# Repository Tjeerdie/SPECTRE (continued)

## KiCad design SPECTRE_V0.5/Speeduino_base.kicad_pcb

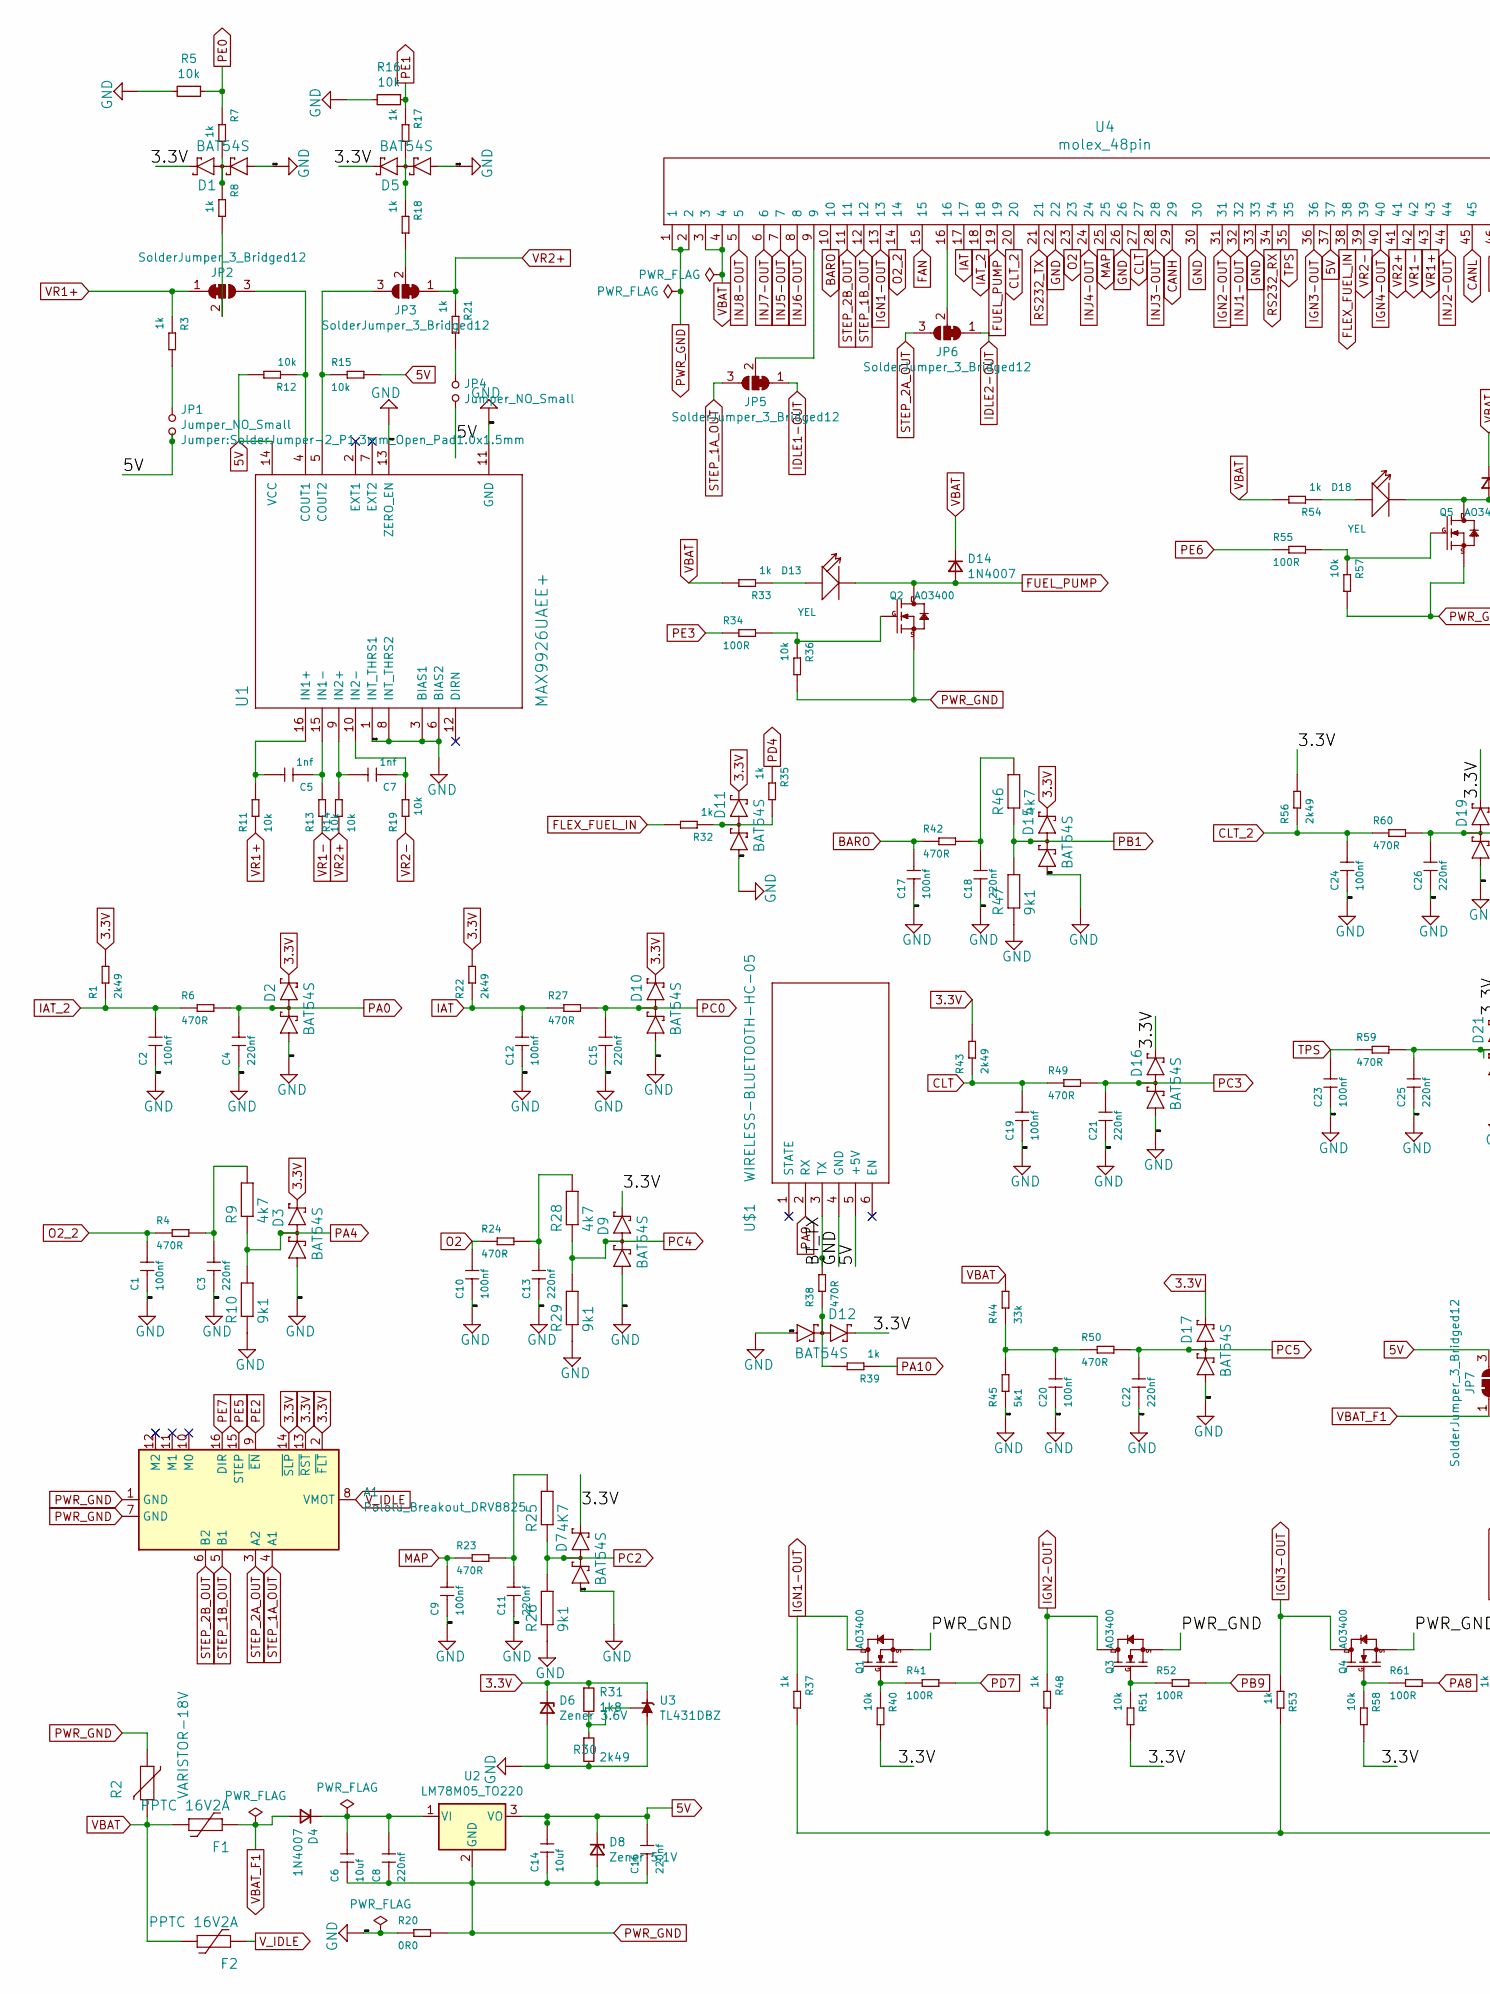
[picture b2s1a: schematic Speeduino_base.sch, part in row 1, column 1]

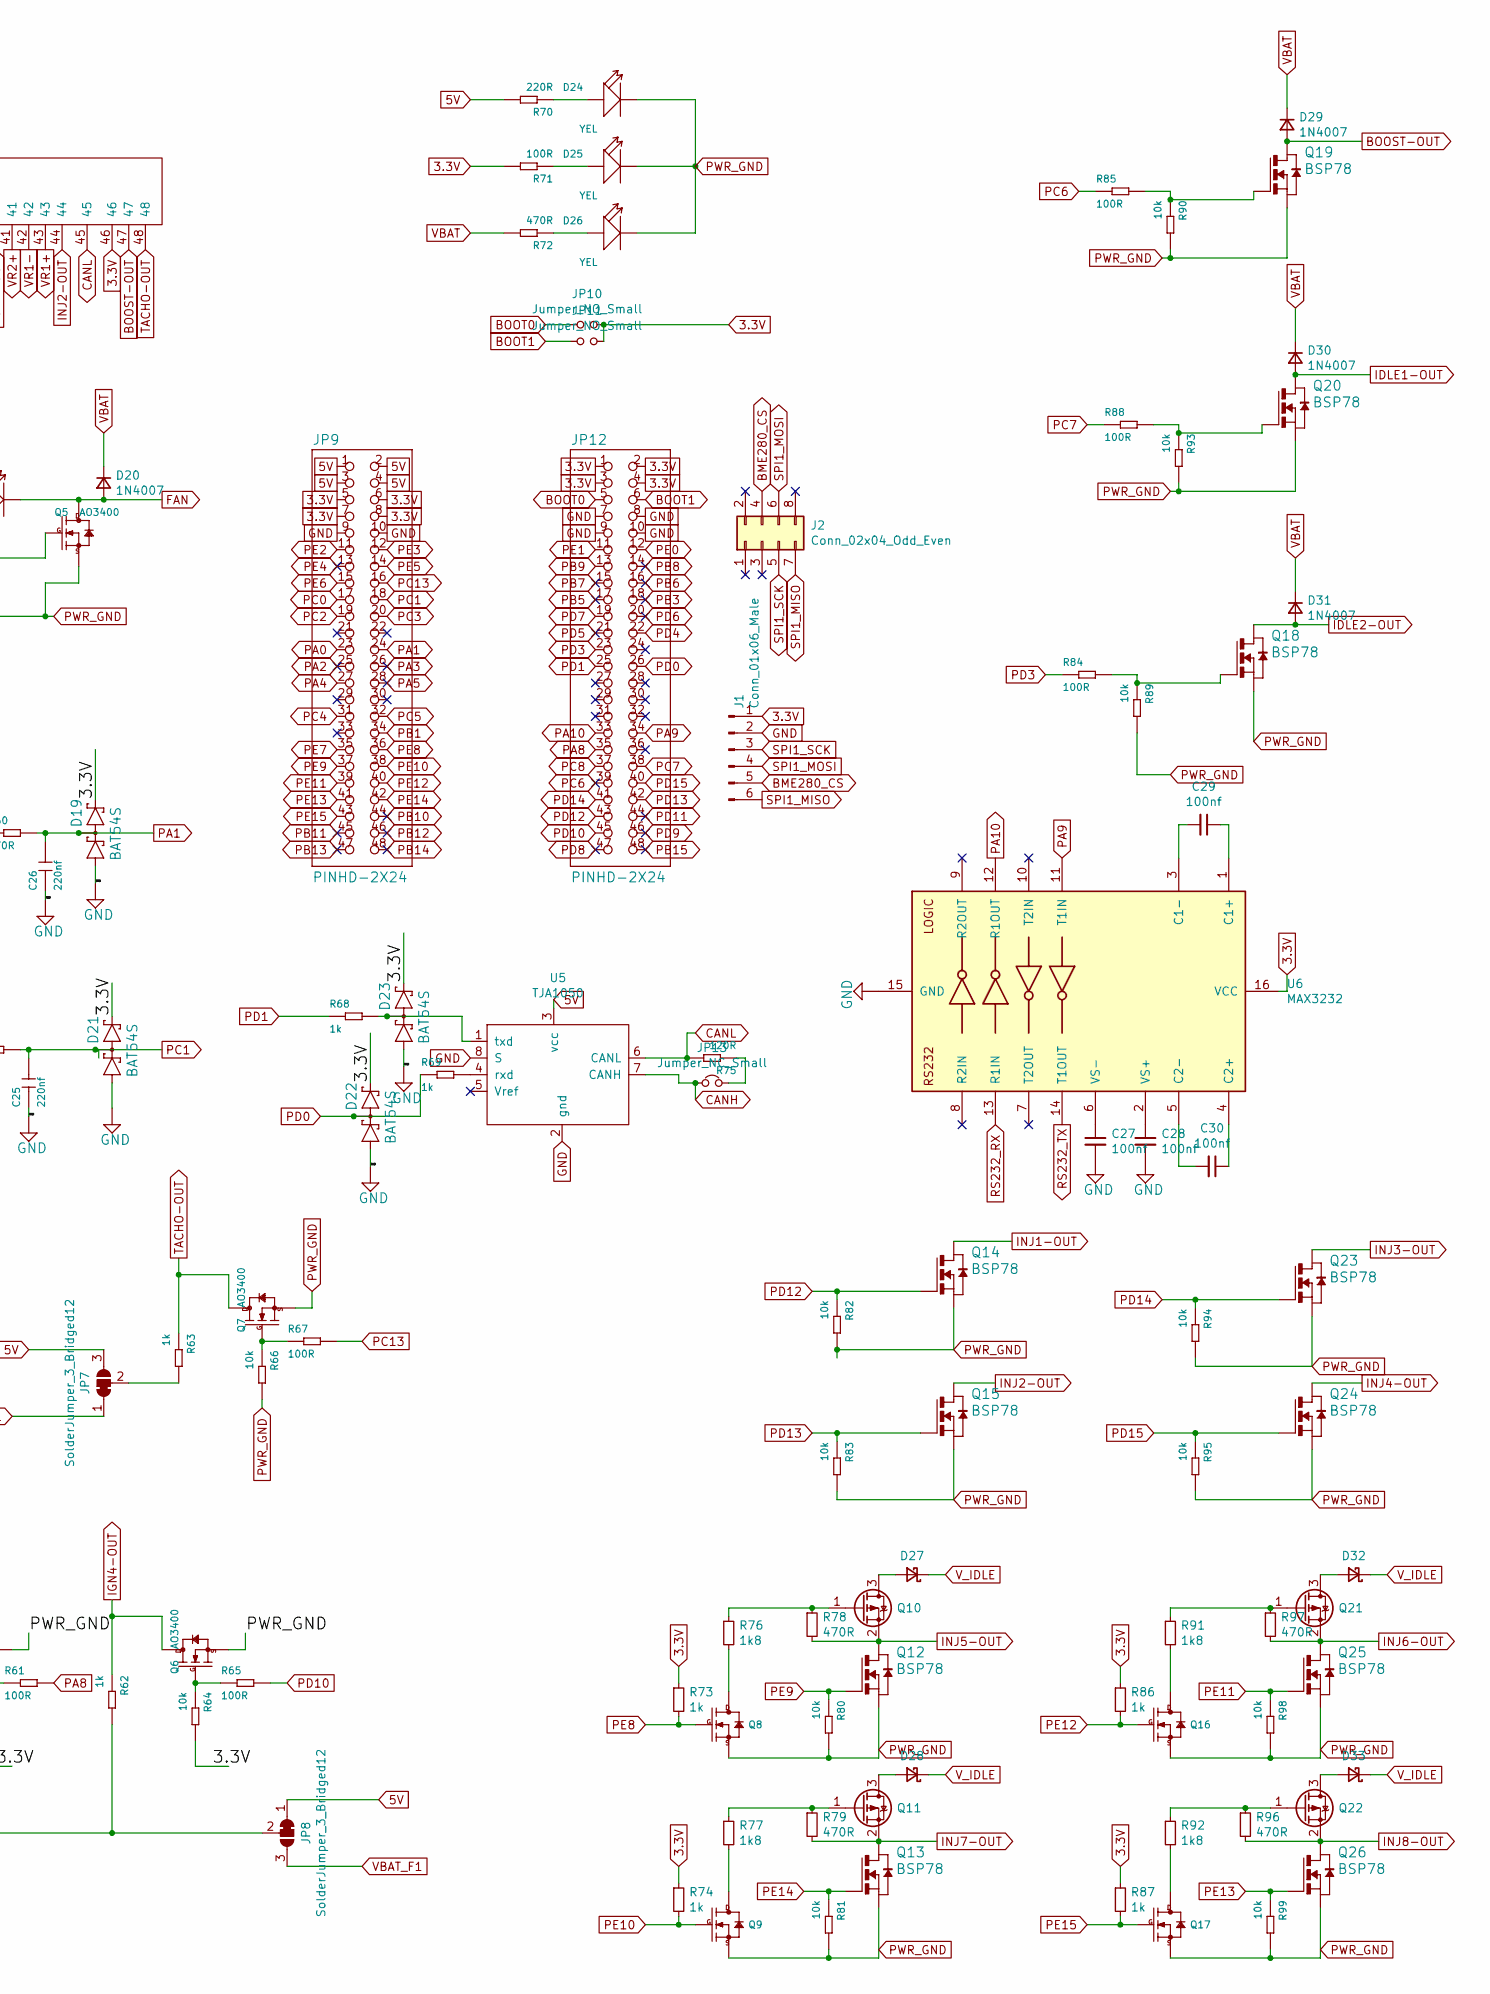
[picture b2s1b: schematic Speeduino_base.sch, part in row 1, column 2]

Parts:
A1: Pololu_Breakout_DRV8825; Pololu_Breakout-16_15.2x20.3mm
C1, C2, C9, C10, C12, C17, C19, C20, C23, C24, C27, C28, C29, C30: 100nf; C0603
C3, C4, C8, C11, C13, C15, C16, C18, C21, C22, C25, C26: 220nf; C0603
C5, C7: 1nf; C0603
C6, C14: 10uf; C1206
D1, D2, D3, D5, D7, D9, D10, D11, D12, D15, D16, D17, D19, D21, D22, D23: BAT54S; SOT23
D4, D14, D20, D27, D28, D29, D30, D31, D32, D33: 1N4007; D_SMA
D6: Zener 3.6V; D_MiniMELF_Handsoldering
D8: Zener 5.1V; D_MiniMELF_Handsoldering
D13, D18, D24, D25, D26: YEL; LED-0603
F1, F2: PPTC 16V2A; R_1812_4532Metric_Pad1.30x3.40mm_HandSolder
J1: Conn_01x06_Male; PinHeader_1x06_P2.54mm_Vertical
J2: Conn_02x04_Odd_Even; PinHeader_2x04_P2.54mm_Vertical
JP1, JP4: Jumper_NO_Small; SolderJumper-2_P1.3mm_Open_Pad1.0x1.5mm
JP2, JP3, JP5, JP6, JP7, JP8: SolderJumper_3_Bridged12; SolderJumper-3_P1.3mm_Bridged12_Pad1.0x1.5mm
JP9, JP12: PINHD-2X24; 2X24
JP10, JP11: Jumper_NO_Small; PinHeader_1x02_P2.54mm_Vertical
JP13: Jumper_NC_Small; SolderJumper-2_P1.3mm_Bridged_Pad1.0x1.5mm
Q1, Q2, Q3, Q4, Q5, Q6, Q7: AO3400; SOT-23
Q8, Q9, Q16, Q17: AO3422; SOT-23_Handsoldering
Q10, Q11, Q21, Q22: AO3401A; SOT-23_Handsoldering
Q12, Q13, Q14, Q15, Q18, Q19, Q20, Q23, Q24, Q25, Q26: BSP78; SOT223
R1, R22, R30, R43, R56: 2k49; R0603
R2: VARISTOR-18V; RV_Disc_D12mm_W3.9mm_P7.5mm
R3, R7, R8, R17, R18, R21, R32, R33, R35, R37, R39, R48, R53, R54, R62, R63, R68, R69, R73, R74, R86, R87: 1k; R0603
R4, R6, R23, R24, R27, R38, R42, R49, R50, R59, R60, R72, R78, R79, R96, R97: 470R; R0603
R5, R11, R12, R13, R14, R15, R16, R19, R36, R40, R51, R57, R58, R64, R66, R80, R81, R82, R83, R89, R90, R93, R94, R95, R98, R99: 10k; R0603
R9, R28, R46: 4k7; R0603
R10, R26, R29, R47: 9k1; R0603
R20: 0R0; R0603
R25: 4K7; R0603
R31, R76, R77, R91, R92: 1k8; R0603
R34, R41, R52, R55, R61, R65, R67, R71, R84, R85, R88: 100R; R0603
R44: 33k; R0603
R45: 5k1; R0603
R70: 220R; R0603
R75: 120R; R0603
U1: MAX9926UAEE+; 21-0055H_16
U2: LM78M05_TO220; TO-220-3_Vertical
U3: TL431DBZ; SOT-23
U4: molex_48pin; Molex_48
U5: TJA1050; SO-8_5.3x6.2mm_P1.27mm
U6: MAX3232; SOIC-16_4.55x10.3mm_P1.27mm
U$1: WIRELESS-BLUETOOTH-HC-05

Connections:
3.3V: A1.2 (~FLT), A1.13 (~RST), A1.14 (~SLP), D1.2 (C2), D2.2 (C2), D3.2 (C2), D5.2 (C2), D6.1 (K), D7.2 (C2), D9.2 (C2), D10.2 (C2), D11.2 (C2), D12.2 (C2), D15.2 (C2), D16.2 (C2), D17.2 (C2), D19.2 (C2), D21.2 (C2), D22.2 (C2), D23.2 (C2), J1.1, JP9.5, JP9.6, JP9.7, JP9.8, JP10.2, JP11.2, JP12.1, JP12.2, JP12.3, JP12.4, R1.2, R22.2, R31.1, R40.2, R43.2, R51.2, R56.2, R58.2, R64.2, R71.2, R73.1, R74.1, R86.1, R87.1, U3.1 (K), U4.46, U6.16 (VCC)
5V: C14.2, C16.2, D8.1 (K), JP1.2, JP4.2, JP7.3 (B), JP8.1 (A), JP9.1, JP9.2, JP9.3, JP9.4, R12.2, R15.2, R70.2, U1.14 (VCC), U2.3 (VO), U4.37, U5.3 (vcc), U$1.5 (+5V)
/BT_TX: R38.2, U$1.3 (TX)
AIN_1: C2.2, R1.1, R6.1, U4.18
AIN_2: C1.2, R4.1, U4.14
AIN_3: C24.2, R56.1, R60.1, U4.20
BARO: C17.2, R42.1, U4.10
BME280_CS: J1.5, J2.4
BOOST-OUT: D29.2 (A), Q19.2 (D), Q19.4 (D), U4.47
BOOT0: JP10.1, JP12.5
BOOT1: JP11.1, JP12.6
CANH: JP13.1, U4.29, U5.7 (CANH)
CANL: R75.2, U4.45, U5.6 (CANL)
CLT: C19.2, R43.1, R49.1, U4.27
FAN: D18.-, D20.2 (A), Q5.3 (D), U4.15
FLEX_FUEL_IN: R32.2, U4.38
FUEL_PUMP: D13.-, D14.2 (A), Q2.3 (D), U4.19
GND: C1.1, C2.1, C3.1, C4.1, C9.1, C10.1, C11.1, C12.1, C13.1, C15.1, C17.1, C18.1, C19.1, C20.1, C21.1, C22.1, C23.1, C24.1, C25.1, C26.1, C27.2, C28.2, D1.1 (A1), D2.1 (A1), D3.1 (A1), D5.1 (A1), D6.2 (A), D7.1 (A1), D9.1 (A1), D10.1 (A1), D11.1 (A1), D12.1 (A1), D15.1 (A1), D16.1 (A1), D17.1 (A1), D19.1 (A1), D21.1 (A1), D22.1 (A1), D23.1 (A1), J1.2, JP9.9, JP9.10, JP12.7, JP12.8, JP12.9, JP12.10, R5.2, R10.1, R16.2, R20.1, R26.1, R29.1, R30.2, R45.1, R47.1, U1.1 (INT_THRS1), U1.3 (BIAS1), U1.6 (BIAS2), U1.8 (INT_THRS2), U1.11 (GND), U1.13 (ZERO_EN), U3.3 (A), U4.22, U4.26, U4.30, U4.33, U5.2 (gnd), U5.8 (S), U6.15 (GND), U$1.4 (GND)
IAT: C12.2, R22.1, R27.1, U4.17
IDLE1-OUT: D30.2 (A), JP5.1 (A), Q20.2 (D), Q20.4 (D)
IDLE2-OUT: D31.2 (A), JP6.1 (A), Q18.2 (D), Q18.4 (D)
IGN1-OUT: Q1.3 (D), R37.1, U4.13
IGN2-OUT: Q3.3 (D), R48.1, U4.31
IGN3-OUT: Q4.3 (D), R53.1, U4.36
IGN4-OUT: Q6.3 (D), R62.1, U4.40
INJ1-OUT: Q14.2 (D), Q14.4 (D), U4.32
INJ2-OUT: Q15.2 (D), Q15.4 (D), U4.44
INJ3-OUT: Q23.2 (D), Q23.4 (D), U4.28
INJ4-OUT: Q24.2 (D), Q24.4 (D), U4.24
INJ5-OUT: Q10.2 (S), Q12.2 (D), Q12.4 (D), R78.2, U4.7
INJ6-OUT: Q21.2 (S), Q25.2 (D), Q25.4 (D), R97.2, U4.8
INJ7-OUT: Q11.2 (S), Q13.2 (D), Q13.4 (D), R79.2, U4.6
INJ8-OUT: Q22.2 (S), Q26.2 (D), Q26.4 (D), R96.2, U4.5
MAP: C9.2, R23.1, U4.25
unnamed: C3.2, R4.2, R9.2
unnamed: C5.1, R13.2, U1.15 (IN1-)
unnamed: C5.2, R11.2, U1.16 (IN1+)
unnamed: C6.2, C8.2, D4.1 (K), U2.1 (VI)
unnamed: C7.1, R19.2, U1.10 (IN2-)
unnamed: C7.2, R14.2, U1.9 (IN2+)
unnamed: C11.2, R23.2, R25.2
unnamed: C13.2, R24.2, R28.2
unnamed: C18.2, R42.2, R46.2
unnamed: C20.2, R44.1, R45.2, R50.1
unnamed: C27.1, U6.6 (VS-)
unnamed: C28.1, U6.2 (VS+)
unnamed: C29.1, U6.1 (C1+)
unnamed: C29.2, U6.3 (C1-)
unnamed: C30.1, U6.4 (C2+)
unnamed: C30.2, U6.5 (C2-)
unnamed: D1.3 (C1A2), R7.2, R8.1
unnamed: D5.3 (C1A2), R17.2, R18.1
unnamed: D11.3 (C1A2), R32.1, R35.2
unnamed: D12.3 (C1A2), R38.1, R39.2
unnamed: D13.+, R33.1
unnamed: D18.+, R54.1
unnamed: D23.3 (C1A2), R68.2, U5.1 (txd)
unnamed: D24.+, R70.1
unnamed: D25.+, R71.1
unnamed: D26.+, R72.1
unnamed: D27.2 (A), Q10.3 (D)
unnamed: D28.2 (A), Q11.3 (D)
unnamed: D32.2 (A), Q21.3 (D)
unnamed: D33.2 (A), Q22.3 (D)
unnamed: JP1.1, R3.2
unnamed: JP2.2 (C), R8.2
unnamed: JP2.3 (B), R12.1, U1.4 (COUT1)
unnamed: JP3.2 (C), R18.2
unnamed: JP3.3 (B), R15.1, U1.5 (COUT2)
unnamed: JP4.1, R21.2
unnamed: JP5.2 (C), U4.9
unnamed: JP6.2 (C), U4.16
unnamed: JP7.2 (C), R63.2
unnamed: JP8.2 (C), R37.2, R48.2, R53.2, R62.2
unnamed: JP13.2, R75.1
unnamed: Q1.1 (G), R40.1, R41.1
unnamed: Q2.1 (G), R34.2, R36.1
unnamed: Q3.1 (G), R51.1, R52.1
unnamed: Q4.1 (G), R58.1, R61.1
unnamed: Q5.1 (G), R55.2, R57.1
unnamed: Q6.1 (G), R64.1, R65.1
unnamed: Q7.1 (G), R66.1, R67.1
unnamed: Q8.3 (D), R76.2
unnamed: Q9.3 (D), R77.2
unnamed: Q10.1 (G), R76.1, R78.1
unnamed: Q11.1 (G), R77.1, R79.1
unnamed: Q16.3 (D), R91.2
unnamed: Q17.3 (D), R92.2
unnamed: Q18.1 (G), R84.2, R89.1
unnamed: Q19.1 (G), R85.2, R90.1
unnamed: Q20.1 (G), R88.2, R93.1
unnamed: Q21.1 (G), R91.1, R97.1
unnamed: Q22.1 (G), R92.1, R96.1
unnamed: R30.1, R31.2, U3.2 (REF)
unnamed: R69.2, U5.4 (rxd)
O2: C10.2, R24.1, U4.23
PA0: C4.2, D2.3 (C1A2), JP9.23, R6.2
PA1: C26.2, D19.3 (C1A2), JP9.24, R60.2
PA2: JP9.25
PA3: JP9.26
PA4: D3.3 (C1A2), JP9.27, R9.1, R10.2
PA5: JP9.28
PA8: JP12.35, R61.2
PA9: JP12.34, U6.11 (T1IN), U$1.2 (RX)
PA10: JP12.33, R39.1, U6.12 (R1OUT)
PB1: D15.3 (C1A2), JP9.34, R46.1, R47.2
PB3: JP12.18
PB5: JP12.17
PB6: JP12.16
PB7: JP12.15
PB8: JP12.14
PB9: JP12.13, R52.2
PB10: JP9.44
PB11: JP9.45
PB12: JP9.46
PB13: JP9.47
PB14: JP9.48
PB15: JP12.48
PC0: C15.2, D10.3 (C1A2), JP9.17, R27.2
PC1: C25.2, D21.3 (C1A2), JP9.18, R59.2
PC2: D7.3 (C1A2), JP9.19, R25.1, R26.2
PC3: C21.2, D16.3 (C1A2), JP9.20, R49.2
PC4: D9.3 (C1A2), JP9.31, R28.1, R29.2
PC5: C22.2, D17.3 (C1A2), JP9.32, R50.2
PC6: JP12.39, R85.1
PC7: JP12.38, R88.1
PC8: JP12.37
PC13: JP9.16, R67.2
PD0: D22.3 (C1A2), JP12.26, R69.1
PD1: JP12.25, R68.1
PD3: JP12.23, R84.1
PD4: JP12.22, R35.1
PD5: JP12.21
PD6: JP12.20
PD7: JP12.19, R41.2
PD8: JP12.47
PD9: JP12.46
PD10: JP12.45, R65.2
PD11: JP12.44
PD12: JP12.43, Q14.1 (G), R82.1
PD13: JP12.42, Q15.1 (G), R83.1
PD14: JP12.41, Q23.1 (G), R94.1
PD15: JP12.40, Q24.1 (G), R95.1
PE0: JP12.12, R5.1, R7.1
PE1: JP12.11, R16.1, R17.1
PE2: A1.9 (~EN), JP9.11
PE3: JP9.12, R34.1
PE4: JP9.13
PE5: A1.15 (STEP), JP9.14
PE6: JP9.15, R55.1
PE7: A1.16 (DIR), JP9.35
PE8: JP9.36, Q8.1 (G), R73.2
PE9: JP9.37, Q12.1 (G), R80.1
PE10: JP9.38, Q9.1 (G), R74.2
PE11: JP9.39, Q25.1 (G), R98.1
PE12: JP9.40, Q16.1 (G), R86.2
PE13: JP9.41, Q26.1 (G), R99.1
PE14: JP9.42, Q13.1 (G), R81.1
PE15: JP9.43, Q17.1 (G), R87.2
PWR_GND: A1.1 (GND), A1.7 (GND), C6.1, C8.1, C14.1, C16.1, D8.2 (A), D24.-, D25.-, D26.-, Q1.2 (S), Q2.2 (S), Q3.2 (S), Q4.2 (S), Q5.2 (S), Q6.2 (S), Q7.2 (S), Q8.2 (S), Q9.2 (S), Q12.3 (S), Q13.3 (S), Q14.3 (S), Q15.3 (S), Q16.2 (S), Q17.2 (S), Q18.3 (S), Q19.3 (S), Q20.3 (S), Q23.3 (S), Q24.3 (S), Q25.3 (S), Q26.3 (S), R2.1, R20.2, R36.2, R57.2, R66.2, R80.2, R81.2, R82.2, R83.2, R89.2, R90.2, R93.2, R94.2, R95.2, R98.2, R99.2, U2.2 (GND), U4.1, U4.2
RS232_RX: U4.34, U6.13 (R1IN)
RS232_TX: U4.21, U6.14 (T1OUT)
SPI1_MISO: J1.6, J2.7
SPI1_MOSI: J1.4, J2.6
SPI1_SCK: J1.3, J2.5
STEP_1A_OUT: A1.4 (A1), JP5.3 (B)
STEP_1B_OUT: A1.5 (B1), U4.12
STEP_2A_OUT: A1.3 (A2), JP6.3 (B)
STEP_2B_OUT: A1.6 (B2), U4.11
TACHO-OUT: Q7.3 (D), R63.1, U4.48
TPS: C23.2, R59.1, U4.35
VBAT: D14.1 (K), D20.1 (K), D29.1 (K), D30.1 (K), D31.1 (K), F1.1, F2.1, R2.2, R33.2, R44.2, R54.2, R72.2, U4.3, U4.4
VBAT_F1: D4.2 (A), F1.2, JP7.1 (A), JP8.3 (B)
VR1+: JP2.1 (A), R3.1, R11.1, U4.43
VR1-: R13.1, U4.42
VR2+: JP3.1 (A), R14.1, R21.1, U4.41
VR2-: R19.1, U4.39
V_IDLE: A1.8 (VMOT), D27.1 (K), D28.1 (K), D32.1 (K), D33.1 (K), F2.2

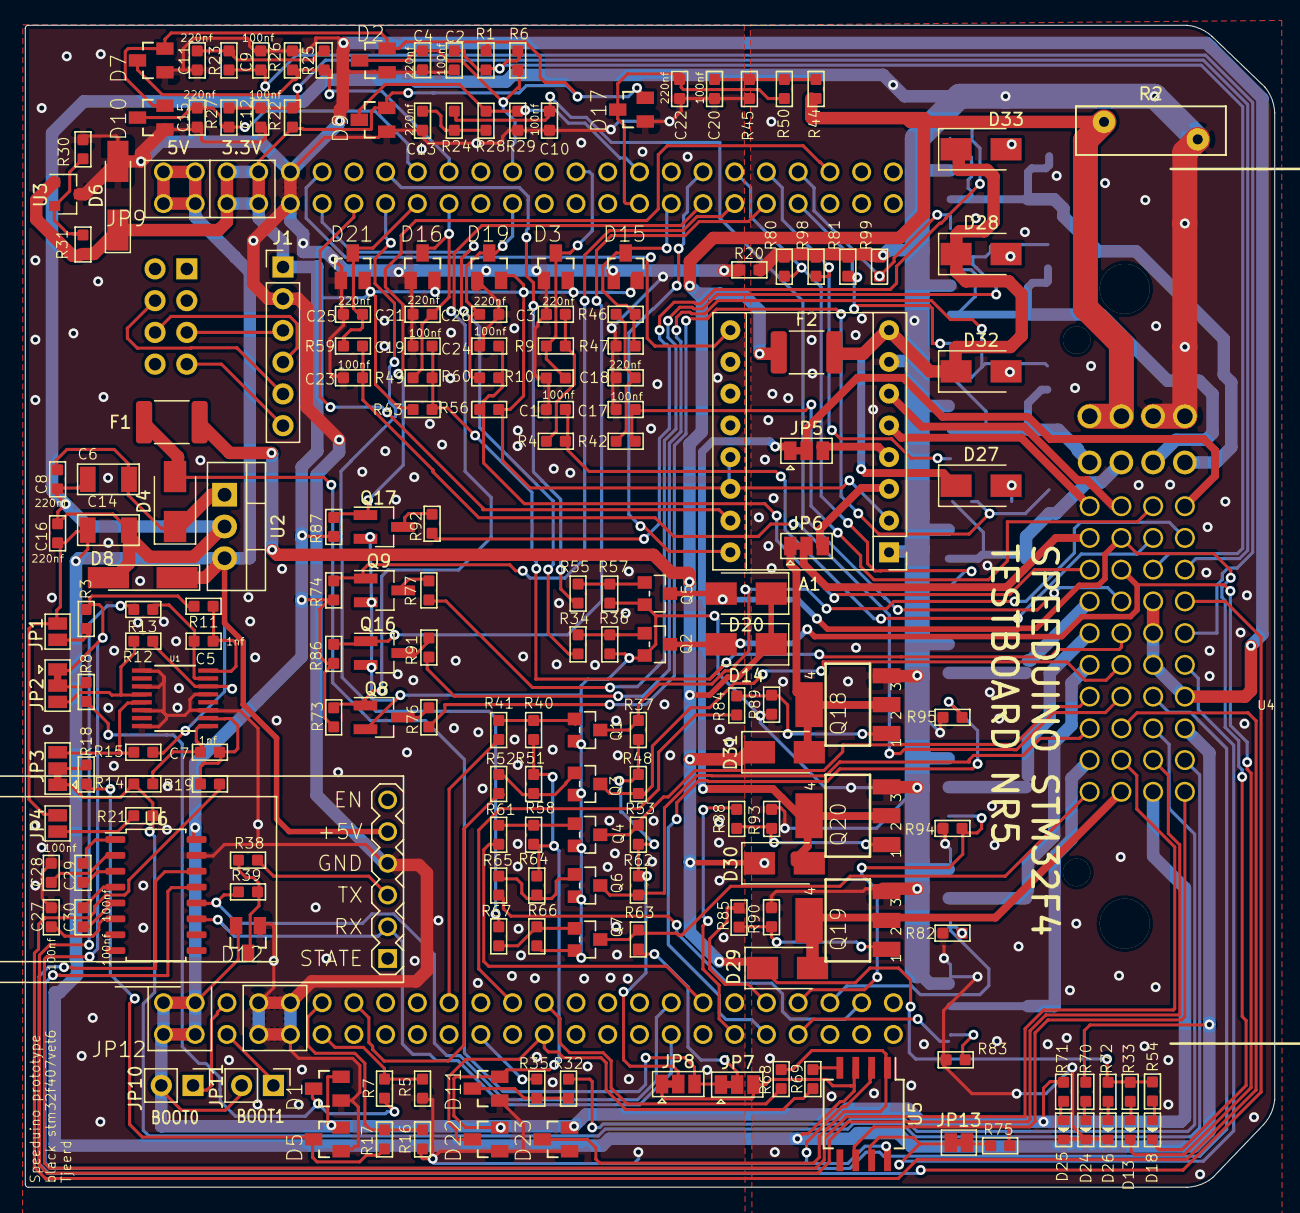
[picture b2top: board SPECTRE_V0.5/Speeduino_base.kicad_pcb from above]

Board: 2 copper layers, 100.0 x 93.0 mm, 213 parts (0 on the bottom side), 157 nets.

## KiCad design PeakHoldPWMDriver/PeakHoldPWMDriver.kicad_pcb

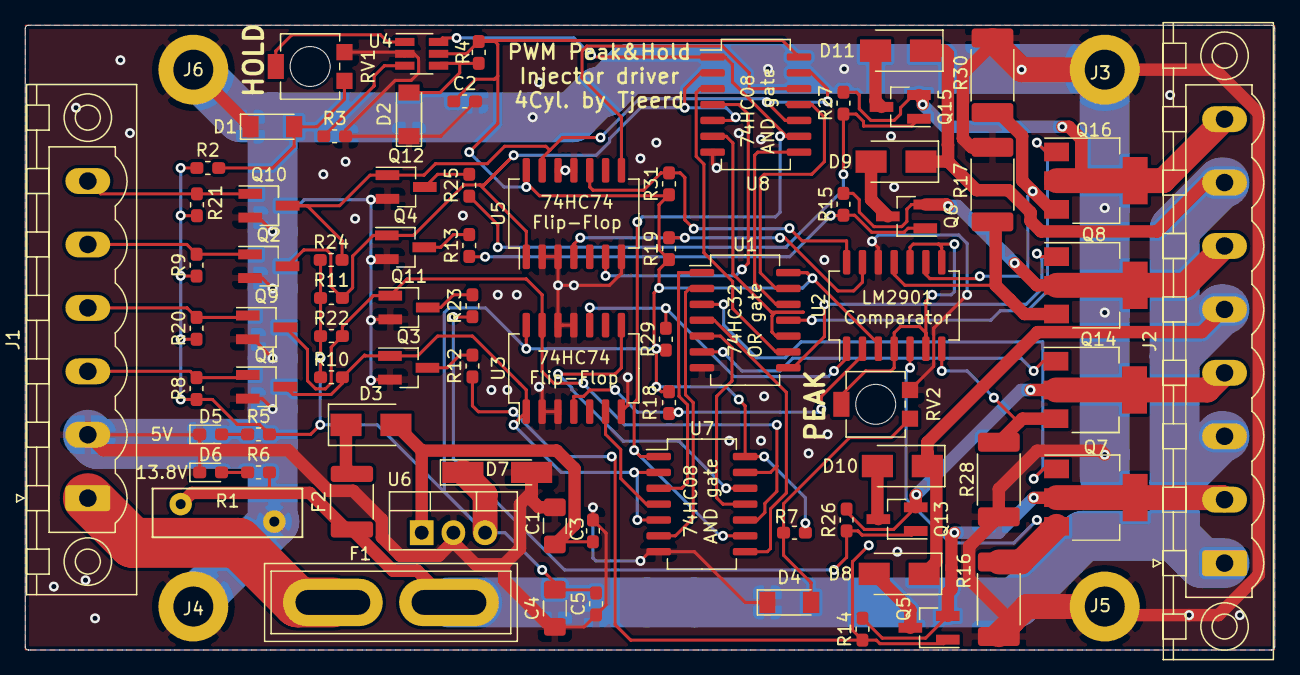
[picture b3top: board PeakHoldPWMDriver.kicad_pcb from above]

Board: 2 copper layers, 100.1 x 50.0 mm, 81 parts (0 on the bottom side), 63 nets.

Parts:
C1, C4: 10uf; C_1206_3216Metric_Pad1.42x1.75mm_HandSolder
C2, C3, C5: 220nf; C_0603_1608Metric_Pad1.05x0.95mm_HandSolder
D1, D4: LL4148; D_MiniMELF
D2: SS310; D_MiniMELF
D3: 40V-1A; D_SMA
D5, D6: BLUE; LED_0603_1608Metric_Pad1.05x0.95mm_HandSolder
D7: D_Zener_Small; D_MiniMELF_Handsoldering
D8, D9, D10, D11: SS310; D_SMA
F1: Fuse; Fuse_Blade_ATO_directSolder
F2: PPTC 16V2A; Fuse_1812_4532Metric_Pad1.30x3.40mm_HandSolder
J1: Screw_Terminal_01x06; PhoenixContact_MSTBV_2,5_6-GF-5,08_1x06_P5.08mm_Vertical_Th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
J2: Screw_Terminal_01x08; PhoenixContact_MSTBV_2,5_8-GF-5,08_1x08_P5.08mm_Vertical_Th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
J3, J4, J5, J6: Mounting 3mm; MountingHole_3.2mm_M3_DIN965_Pad
Q1, Q2, Q9, Q10: AO3400; SOT-23_Handsoldering
Q3, Q4, Q11, Q12: AO3422; SOT-23_Handsoldering
Q5, Q6, Q13, Q15: AO3401A; SOT-23_Handsoldering
Q7, Q8, Q14, Q16: BSP78; SOT-223
R1: VARISTOR-18V; RV_Disc_D12mm_W3.9mm_P7.5mm
R2, R7, R14, R15, R26, R27: 470; R_0603_1608Metric_Pad1.05x0.95mm_HandSolder
R3, R4: 500k; R_0603_1608Metric_Pad1.05x0.95mm_HandSolder
R5: 180; R_0603_1608Metric_Pad1.05x0.95mm_HandSolder
R6: 560; R_0603_1608Metric_Pad1.05x0.95mm_HandSolder
R8, R9, R18, R19, R20, R21, R29, R31: 1K; R_0603_1608Metric_Pad1.05x0.95mm_HandSolder
R10, R11, R22, R24: 10K; R_0603_1608Metric_Pad1.05x0.95mm_HandSolder
R12, R13, R23, R25: 1K8; R_0603_1608Metric_Pad1.05x0.95mm_HandSolder
R16, R17, R28, R30: 0R1; R_2512_6332Metric_Pad1.52x3.35mm_HandSolder
RV1, RV2: R_POT_Small; Potentiometer_Bourns_3314R-1_Vertical_Hole
U1: 74LS32; SO-14_5.3x10.2mm_P1.27mm
U2: LM2901; SO-14_5.3x10.2mm_P1.27mm
U3, U5: 74LS74; SO-14_5.3x10.2mm_P1.27mm
U4: LTC6992; SOT-23-6_Handsoldering
U6: LM78M05_TO220; TO-220-3_Vertical
U7, U8: 74LS08; SO-14_5.3x10.2mm_P1.27mm

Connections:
5V: C2.1, C4.2, C5.2, D7.1, R2.1, R4.1, R5.2, R7.1, R8.1, R9.1, R10.1, R11.1, R18.1, R19.1, R20.1, R21.1, R22.1, R24.1, R29.1, R31.1, U1.14, U2.3, U3.14, U4.5, U5.14, U6.3, U7.14, U8.14
INJ1: J1.3, Q1.1, R8.2
INJ1-OUT: J2.2, Q5.2, Q7.2, Q7.4, R14.2
INJ2: J1.4, Q9.1, R20.2
INJ2-OUT: J2.4, Q13.2, Q14.2, Q14.4, R26.2
INJ3: J1.5, Q2.1, R9.2
INJ3-OUT: J2.6, Q6.2, Q8.2, Q8.4, R15.2
INJ4: J1.6, Q10.1, R21.2
INJ4-OUT: J2.8, Q15.2, Q16.2, Q16.4, R27.2
unnamed: C1.2, C3.2, D3.2, U6.1
unnamed: D1.2, R2.2, RV1.1
unnamed: D2.2, R4.2, U4.4
unnamed: D3.1, F2.2
unnamed: D4.2, R7.2, RV2.1
unnamed: D5.2, R5.1
unnamed: D6.2, R6.1
unnamed: D8.2, Q5.3
unnamed: D9.2, Q6.3
unnamed: D10.2, Q13.3
unnamed: D11.2, Q15.3
unnamed: Q3.3, R12.2
unnamed: Q4.3, R13.2
unnamed: Q5.1, R12.1, R14.1
unnamed: Q6.1, R13.1, R15.1
unnamed: Q7.1, U1.3
unnamed: Q7.3, R16.1, U2.5
unnamed: Q8.1, U1.8
unnamed: Q8.3, R17.1, U2.11
unnamed: Q11.3, R23.2
unnamed: Q12.3, R25.2
unnamed: Q13.1, R23.1, R26.1
unnamed: Q14.1, U1.6
unnamed: Q14.3, R28.1, U2.7
unnamed: Q15.1, R25.1, R27.1
unnamed: Q16.1, U1.11
unnamed: Q16.3, R30.1, U2.9
unnamed: R3.1, U4.3
unnamed: R18.2, U2.2, U3.4
unnamed: R19.2, U2.13, U5.4
unnamed: R29.2, U2.1, U3.10
unnamed: R31.2, U2.14, U5.10
unnamed: RV1.2, U4.1
unnamed: U1.1, U7.3
unnamed: U1.2, U7.6
unnamed: U1.4, U7.8
unnamed: U1.5, U7.11
unnamed: U1.9, U8.3
unnamed: U1.10, U8.6
unnamed: U1.12, U8.8
unnamed: U1.13, U8.11
unnamed: U3.6, U7.4
unnamed: U3.8, U7.12
unnamed: U5.6, U8.4
unnamed: U5.8, U8.12
PWM: U4.6, U7.1, U7.9, U8.1, U8.9
PWR_GND: C1.1, C2.2, C3.1, C4.1, C5.1, D1.1, D2.1, D4.1, D5.1, D6.1, D7.2, J1.2, J3.1, J4.1, J5.1, J6.1, Q1.2, Q2.2, Q3.2, Q4.2, Q9.2, Q10.2, Q11.2, Q12.2, R1.1, R3.2, R16.2, R17.2, R28.2, R30.2, RV1.3, RV2.3, U1.7, U2.12, U3.2, U3.3, U3.7, U3.11, U3.12, U4.2, U5.2, U5.3, U5.7, U5.11, U5.12, U6.2, U7.7, U8.7
VBAT: D8.1, D9.1, D10.1, D11.1, F1.2, F2.1, J2.1, J2.3, J2.5, J2.7, R1.2, R6.2
VBAT_IN: F1.1, J1.1
VREF: RV2.2, U2.4, U2.6, U2.8, U2.10
inv_INJ1: Q1.3, Q3.1, R10.2, U3.1, U7.2, U7.5
inv_INJ2: Q9.3, Q11.1, R22.2, U3.13, U7.10, U7.13
inv_INJ3: Q2.3, Q4.1, R11.2, U5.1, U8.2, U8.5
inv_INJ4: Q10.3, Q12.1, R24.2, U5.13, U8.10, U8.13
